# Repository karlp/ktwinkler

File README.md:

# kTwinkler

Replacement controller board for some "common" battery powered led fairy lights...

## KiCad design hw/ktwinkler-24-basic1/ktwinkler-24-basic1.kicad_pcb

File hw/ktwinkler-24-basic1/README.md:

# twinkler 24V garden
24v "field" bus lying around the garden, for smallish wires and enough power.
5V "led" bus light for the light strings I know I have
3.3v for an esp32
2x antiparallel led channels. (maybe a third if I can juggle the pins)
ufl antenna mount by default, but onboard PIFA as well.
designed to fit into some cheapish aliexpress waterproof junction boxes

# Bugs
This version won't boot with only the USB supply, it sags too much on startup.
This is because I didn't put enough decoupling on the esp32-c3.  Adding 10uF at
pin2 and 10uF at pin 31 fixed it, and is more inline with the hardware design guidelines
I believe earlier hardware had been sharing input caps with other portions of the boards,
so it wasn't noticed.

# Enhancements for a future version
* Remember rememeber, always add a nice place for a ground clip.
* you put a 3A supply down, it might have been nice to provide an output for that supply, instead
  of just burying it and only using it to power the drivers.

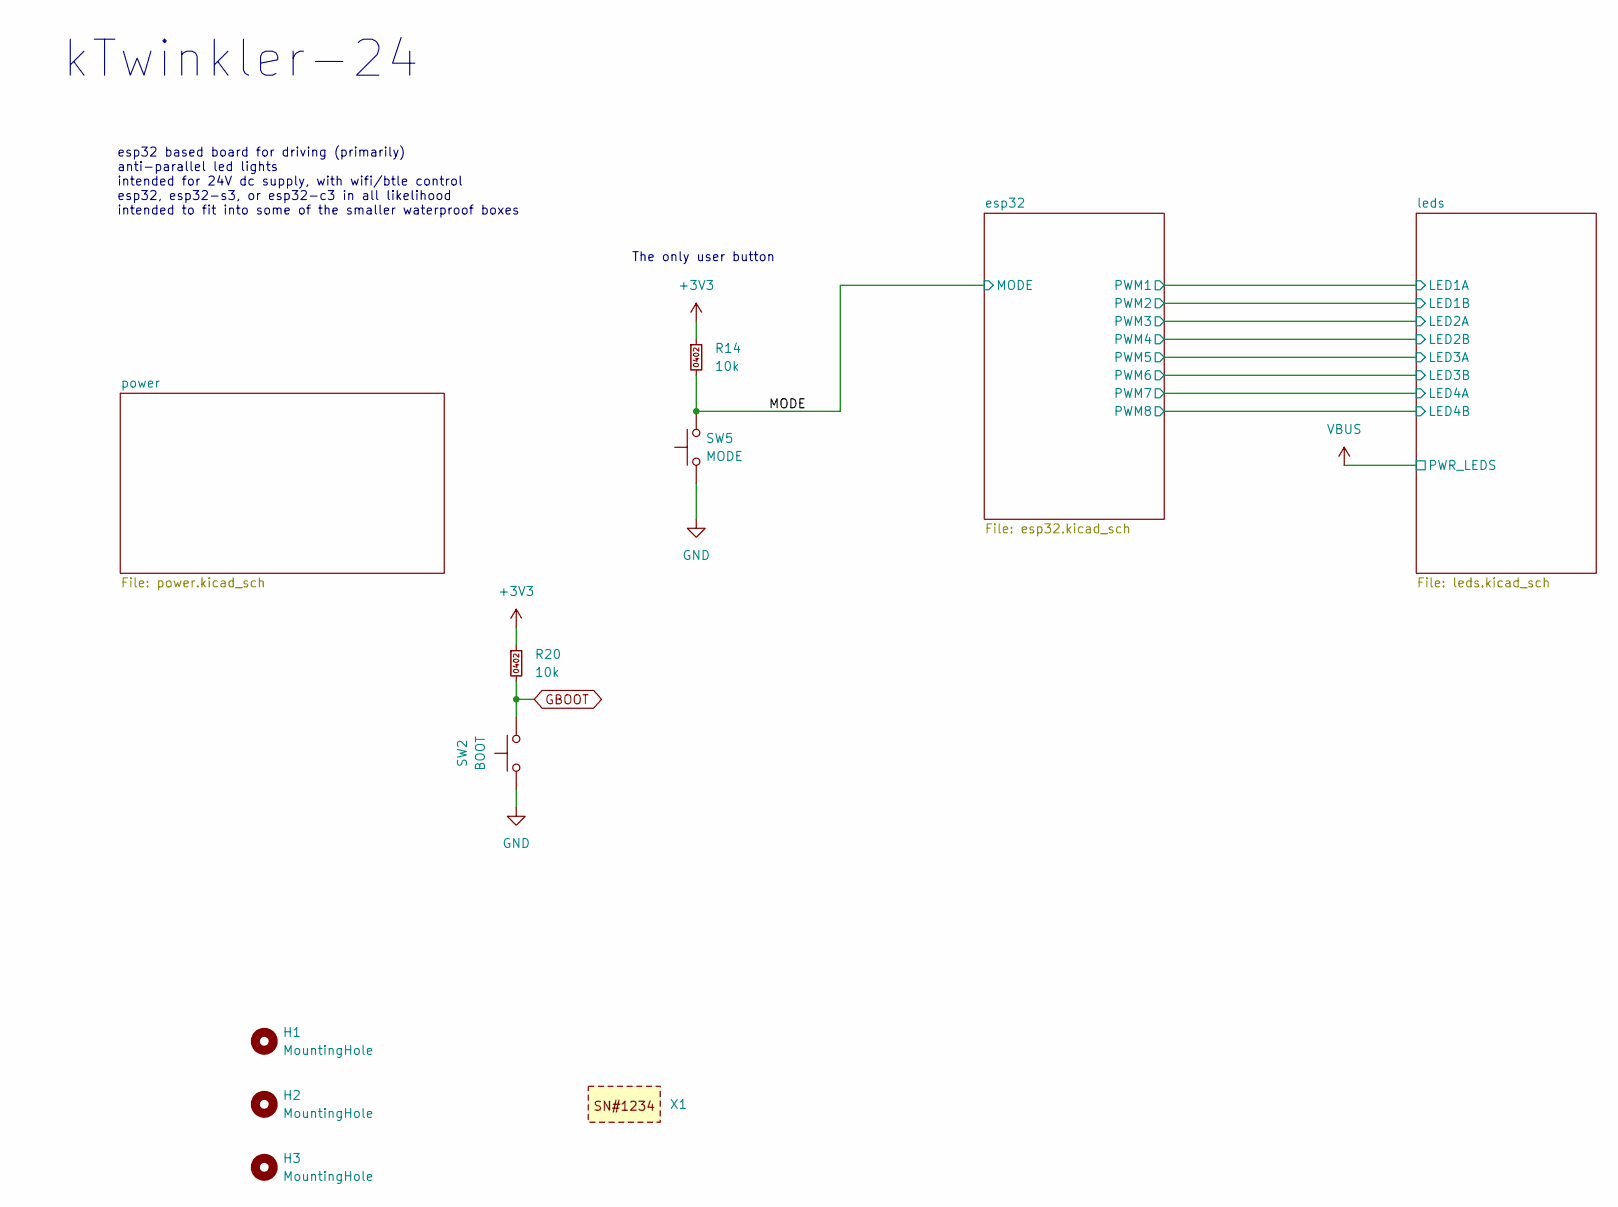
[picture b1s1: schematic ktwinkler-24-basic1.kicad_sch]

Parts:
H1, H2, H3: MountingHole; MountingHole_3.2mm_M3
R14, R20: 10k; R_0402_1005Metric; MPN 0402WGF1002TCE; LCSC Part # C25744
SW2: BOOT; SW_SPST_TL3342; MPN TS-1187A-B-A-B; jlcbasic basic
SW5: MODE; SW_SPST_TL3342; MPN TS-1187A-B-A-B; jlcbasic basic
X1: JLC_2D_BARCODE_8x8mm

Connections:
+3V3: R14.1, R20.1; also elsewhere on the board
/MODE: R14.2, SW5.2; also elsewhere on the board
GBOOT: R20.2, SW2.2; also elsewhere on the board
GND: SW2.1, SW5.1; also elsewhere on the board

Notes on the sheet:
esp32 based board for driving (primarily) anti-parallel led lights intended for 24V dc supply, with wifi/btle control esp32, esp32-s3, or esp32-c3 in all likelihood intended to fit into some of the smaller waterproof boxes
kTwinkler-24
The only user button

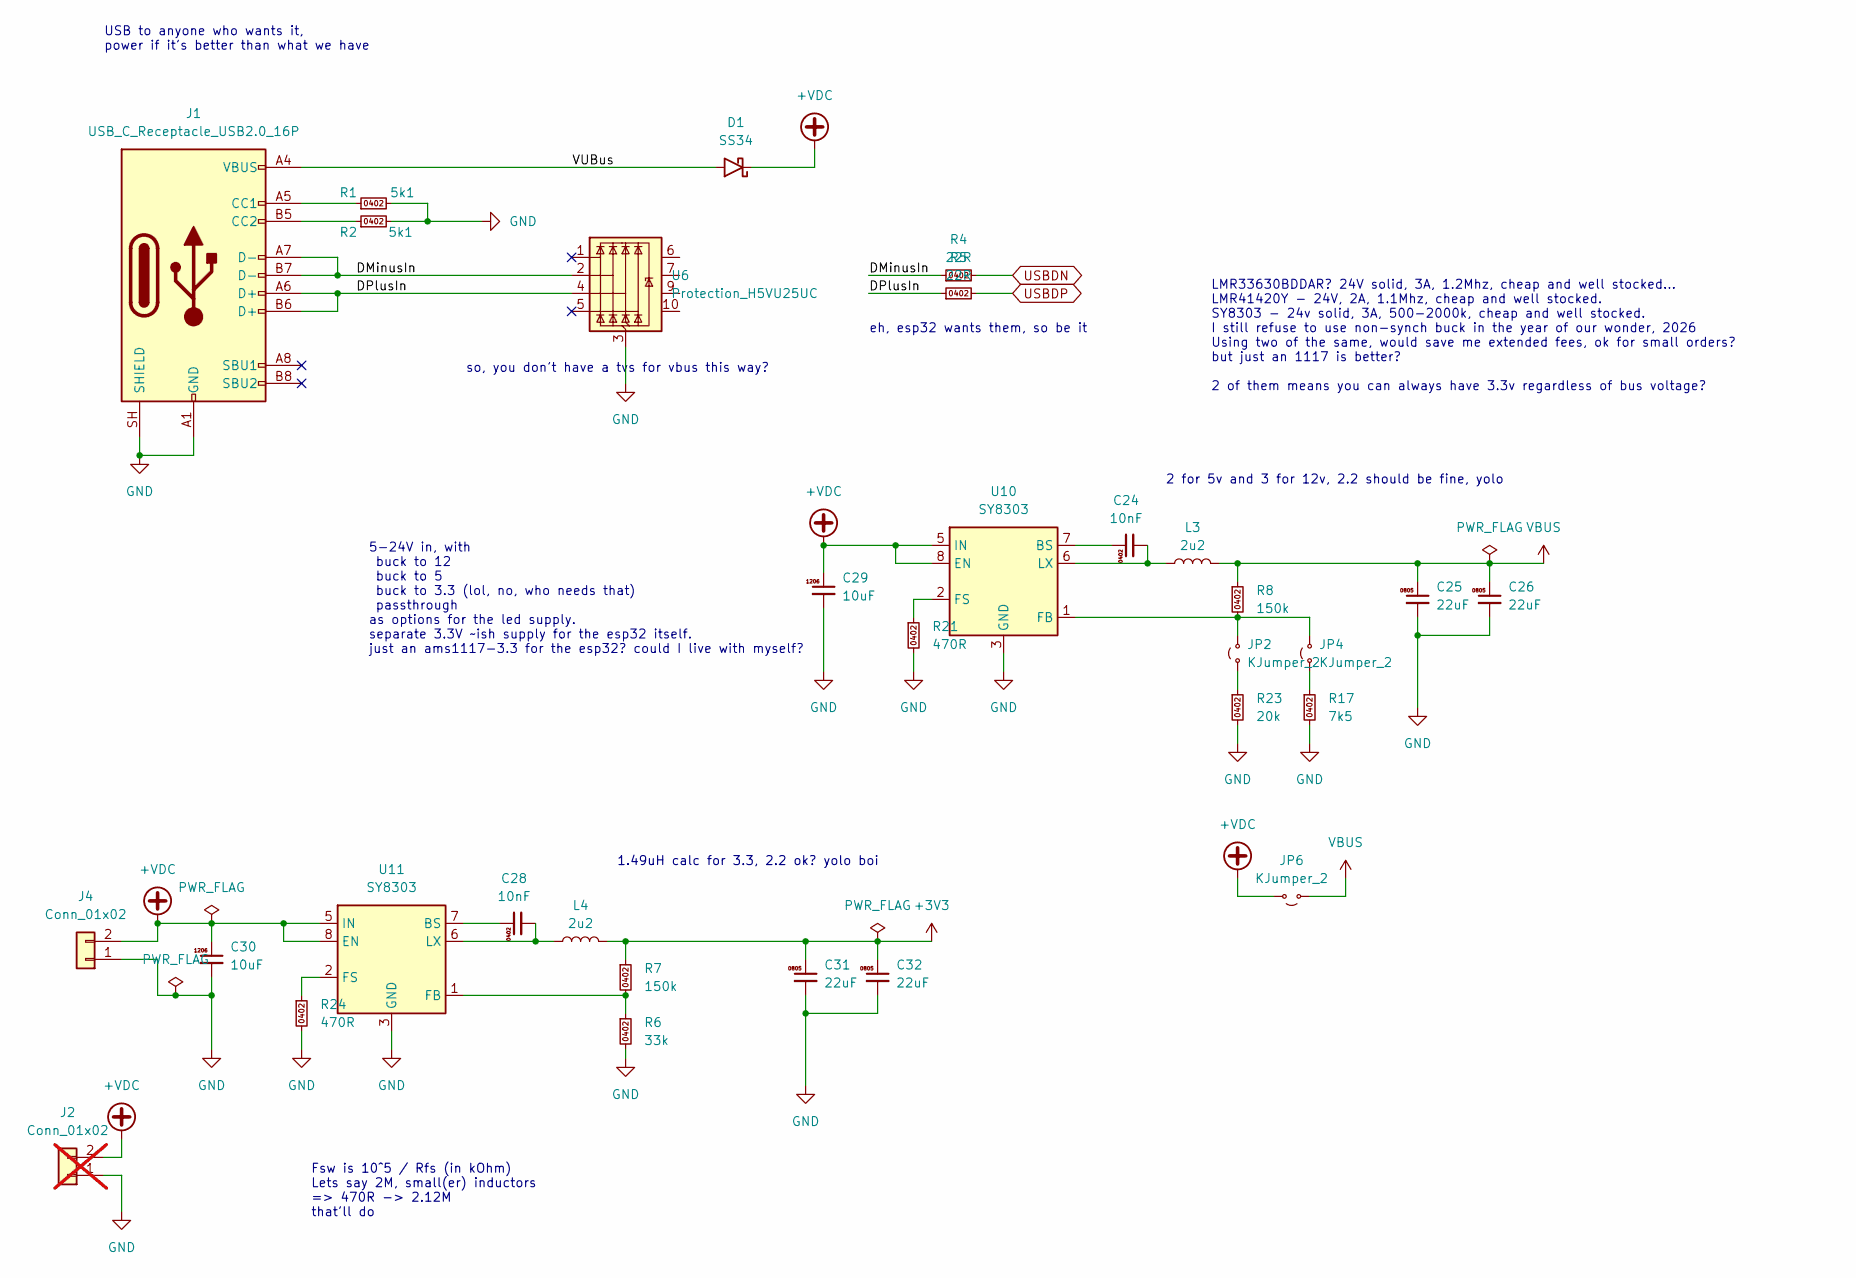
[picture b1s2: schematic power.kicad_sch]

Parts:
C24, C28: 10nF; C_0402_1005Metric; MPN CL05B103KB5NNNC; LCSC Part # C15195
C25, C26, C31, C32: 22uF; C_0805_2012Metric; MPN CL21A226MAQNNNE; LCSC Part # C45783
C29, C30: 10uF; C_1206_3216Metric; MPN CL31A106KBHNNNE; LCSC Part # C13585
D1: SS34; D_SMA; MPN SS34; LCSC Part # C8678
J1: USB_C_Receptacle_USB2.0_16P; USB_C_Receptacle_GCT_USB4105-xx-A_16P_TopMnt_Horizontal; MPN GT-USB-7010ASV; LCSC Part # C2988369
J2: Conn_01x02; PinHeader_1x02_P2.54mm_Vertical; not fitted
J4: Conn_01x02; PhoenixContact_MCV_1,5_2-G-3.81_1x02_P3.81mm_Vertical; MPN WJ15EDGVC-3.81-02P-14-00A; LCSC Part # C8396
JP2, JP4, JP6: KJumper_2; PinHeader_1x02_P2.54mm_Vertical
L3, L4: 2u2; L_Changjiang_FNR4030S; MPN FNR4030S2R2MT; LCSC Part # C167869
R1, R2: 5k1; R_0402_1005Metric; MPN 0402WGF5101TCE; LCSC Part # C25905
R4, R5: 22R; R_0402_1005Metric; MPN 0402WGF220JTCE; LCSC Part # C25092
R6: 33k; R_0402_1005Metric; MPN 0402WGF3302TCE; LCSC Part # C25779
R7, R8: 150k; R_0402_1005Metric; MPN 0402WGF1503TCE; LCSC Part # C25755
R17: 7k5; R_0402_1005Metric; MPN 0402WGF7501TCE; LCSC Part # C25918
R21, R24: 470R; R_0402_1005Metric; MPN 0402WGF4700TCE; LCSC Part # C25117
R23: 20k; R_0402_1005Metric; MPN 0402WGF2002TCE; LCSC Part # C25765
U6: Protection_H5VU25UC; Diodes_UDFN-10_1x2.5mm_P0.5mm; MPN H5VU25UC; jlcbasic preferred
U10, U11: SY8303; TSOT-23-8; LCSC Part # C97054

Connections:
+3V3: C31.1, C32.1, L4.2, R7.1; also elsewhere on the board
+VDC: C29.1, C30.1, D1.1 (K), J2.2, J4.2, JP6.2 (B), U10.5 (IN), U10.8 (EN), U11.5 (IN), U11.8 (EN)
/power/DMinusIn: J1.A7 (D-), J1.B7 (D-), R4.1, U6.2 (I/O2)
/power/DPlusIn: J1.A6 (D+), J1.B6 (D+), R5.1, U6.4 (I/O3)
/power/VUBus: D1.2 (A), J1.A4 (VBUS), J1.A9 (VBUS), J1.B4 (VBUS), J1.B9 (VBUS)
GND: C25.2, C26.2, C29.2, C30.2, C31.2, C32.2, J1.A1 (GND), J1.A12 (GND), J1.B1 (GND), J1.B12 (GND), J1.SH (SHIELD), J2.1, J4.1, R1.2, R2.2, R6.2, R17.2, R21.2, R23.2, R24.2, U6.3 (GND), U6.8 (GND), U10.3 (GND), U10.4 (GND), U11.3 (GND), U11.4 (GND); also elsewhere on the board
unnamed: J1.A5 (CC1), R1.1
unnamed: J1.B5 (CC2), R2.1
unnamed: JP2.1 (A), R23.1
unnamed: JP2.2 (B), JP4.2 (B), R8.2, U10.1 (FB)
unnamed: JP4.1 (A), R17.1
unnamed: C24.1, U10.7 (BS)
unnamed: R21.1, U10.2 (FS)
unnamed: C24.2, L3.1, U10.6 (LX)
unnamed: C28.1, U11.7 (BS)
unnamed: R6.1, R7.2, U11.1 (FB)
unnamed: R24.1, U11.2 (FS)
unnamed: C28.2, L4.1, U11.6 (LX)
USBDN: R4.2; also elsewhere on the board
USBDP: R5.2; also elsewhere on the board
VBUS: C25.1, C26.1, JP6.1 (A), L3.2, R8.1; also elsewhere on the board

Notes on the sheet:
LMR33630BDDAR? 24V solid, 3A, 1.2Mhz, cheap and well stocked... LMR41420Y - 24V, 2A, 1.1Mhz, cheap and well stocked. SY8303 - 24v solid, 3A, 500-2000k, cheap and well stocked. I still refuse to use non-synch buck in the year of our wonder, 2026 Using two of the same, would save me extended fees, ok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
5-24V in, with buck to 12 buck to 5 buck to 3.3 (lol, no, who needs that) passthrough as options for the led supply. separate 3.3V ~ish supply for the esp32 itself. just an ams1117-3.3 for the esp32? could I live with myself?
USB to anyone who wants it, power if it's better than what we have
so, you don't have a tvs for vbus this way?
1.49uH calc for 3.3, 2.2 ok? yolo boi
Fsw is 10^5 / Rfs (in kOhm) Lets say 2M, small(er) inductors => 470R -> 2.12M that'll do
eh, esp32 wants them, so be it
2 for 5v and 3 for 12v, 2.2 should be fine, yolo

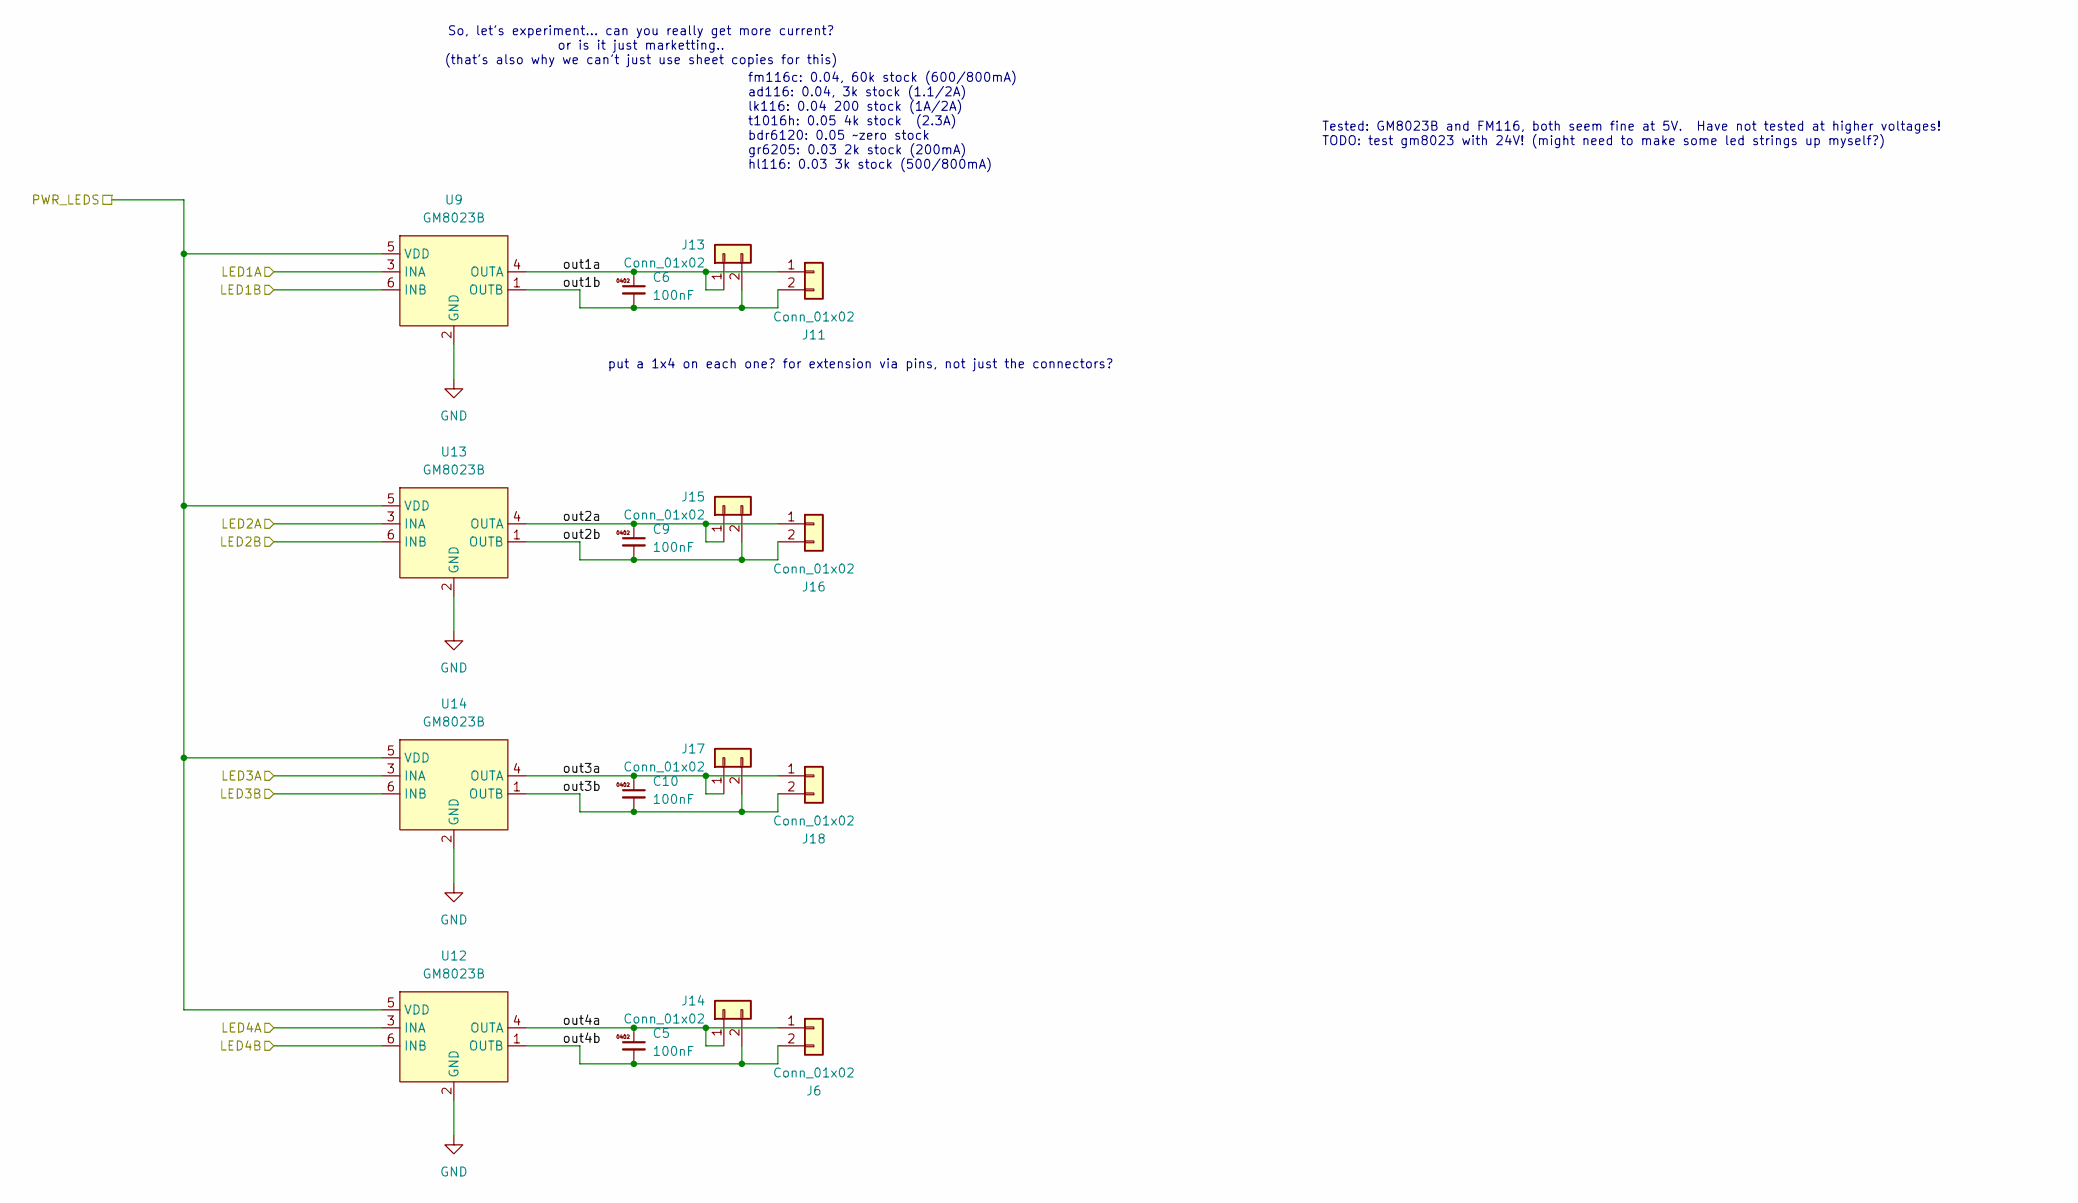
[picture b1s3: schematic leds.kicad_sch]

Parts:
C5, C6, C9, C10: 100nF; C_0402_1005Metric; MPN CL05B104KO5NNNC; LCSC Part # C1525
J6, J11, J16, J18: Conn_01x02; PhoenixContact_MCV_1,5_2-G-3.81_1x02_P3.81mm_Vertical; MPN WJ15EDGVC-3.81-02P-14-00A; LCSC Part # C8396
J13, J14, J15, J17: Conn_01x02; TestPoint_2Pads_Pitch2.54mm_Drill0.8mm
U9, U12, U13, U14: GM8023B; SOT-23-6; MPN GM8023B; LCSC Part # C269871

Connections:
/esp32/PWM1: U9.3 (INA); also elsewhere on the board
/esp32/PWM2: U9.6 (INB); also elsewhere on the board
/esp32/PWM3: U13.3 (INA); also elsewhere on the board
/esp32/PWM4: U13.6 (INB); also elsewhere on the board
/esp32/PWM5: U14.3 (INA); also elsewhere on the board
/esp32/PWM6: U14.6 (INB); also elsewhere on the board
/esp32/PWM7: U12.3 (INA); also elsewhere on the board
/esp32/PWM8: U12.6 (INB); also elsewhere on the board
/leds/out1a: C6.1, J11.1, J13.1, U9.4 (OUTA)
/leds/out1b: C6.2, J11.2, J13.2, U9.1 (OUTB)
/leds/out2a: C9.1, J15.1, J16.1, U13.4 (OUTA)
/leds/out2b: C9.2, J15.2, J16.2, U13.1 (OUTB)
/leds/out3a: C10.1, J17.1, J18.1, U14.4 (OUTA)
/leds/out3b: C10.2, J17.2, J18.2, U14.1 (OUTB)
/leds/out4a: C5.1, J6.1, J14.1, U12.4 (OUTA)
/leds/out4b: C5.2, J6.2, J14.2, U12.1 (OUTB)
GND: U9.2 (GND), U12.2 (GND), U13.2 (GND), U14.2 (GND); also elsewhere on the board
VBUS: U9.5 (VDD), U12.5 (VDD), U13.5 (VDD), U14.5 (VDD); also elsewhere on the board

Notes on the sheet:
So, let's experiment... can you really get more current? or is it just marketting.. (that's also why we can't just use sheet copies for this)
put a 1x4 on each one? for extension via pins, not just the connectors?
fm116c: 0.04, 60k stock (600/800mA) ad116: 0.04, 3k stock (1.1/2A) lk116: 0.04 200 stock (1A/2A) t1016h: 0.05 4k stock (2.3A) bdr6120: 0.05 ~zero stock gr6205: 0.03 2k stock (200mA) hl116: 0.03 3k stock (500/800mA)
Tested: GM8023B and FM116, both seem fine at 5V. Have not tested at higher voltages! TODO: test gm8023 with 24V! (might need to make some led strings up myself?)

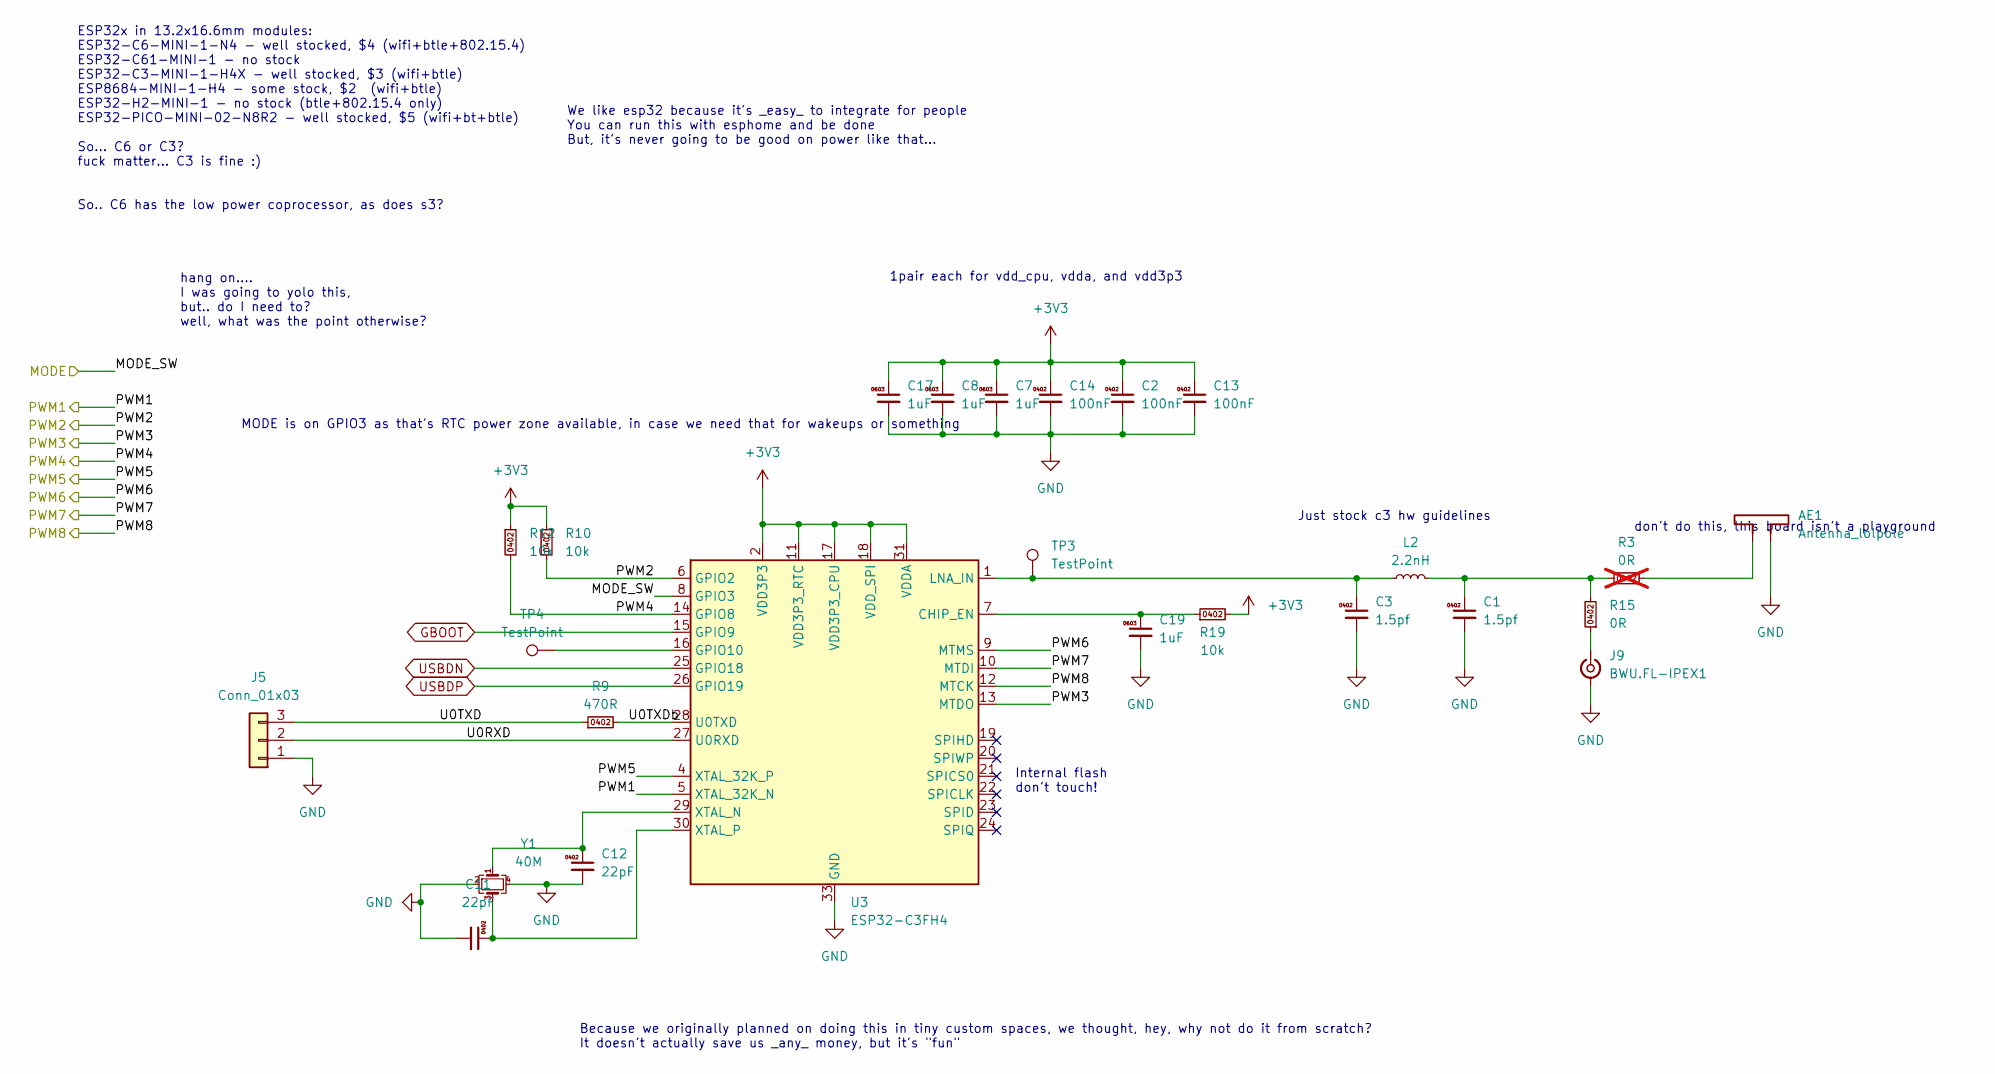
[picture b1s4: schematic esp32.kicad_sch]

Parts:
AE1: Antenna_lolpole; Texas_SWRA117D_2.4GHz_Left
C1, C3: 1.5pf; C_0402_1005Metric; MPN 0402CG1R5C500NT; LCSC Part # C1552
C2, C13, C14: 100nF; C_0402_1005Metric; MPN CL05B104KO5NNNC; LCSC Part # C1525
C7, C8, C17, C19: 1uF; C_0603_1608Metric; MPN CL10A105KB8NNNC; LCSC Part # C15849
C11, C12: 22pF; C_0402_1005Metric; MPN 0402CG220J500NT; LCSC Part # C1555
J5: Conn_01x03; PinHeader_1x03_P2.54mm_Vertical
J9: BWU.FL-IPEX1; U.FL_Hirose_U.FL-R-SMT-1_Vertical; MPN BWU.FL-IPEX1; LCSC Part # C5137195
L2: 2.2nH; L_0402_1005Metric; MPN LQG15HS2N2S02D; LCSC Part # C86061
R3: 0R; R_0402_1005Metric; MPN 0402WGF0000TCE; LCSC Part # C17168; not fitted
R9: 470R; R_0402_1005Metric; MPN 0402WGF4700TCE; LCSC Part # C25117
R10, R12, R19: 10k; R_0402_1005Metric; MPN 0402WGF1002TCE; LCSC Part # C25744
R15: 0R; R_0402_1005Metric; MPN 0402WGF0000TCE; LCSC Part # C17168
TP3, TP4: TestPoint; TestPoint_Pad_D1.0mm
U3: ESP32-C3FH4; QFN-32-1EP_5x5mm_P0.5mm_EP3.7x3.7mm; MPN ESP32-C3FH4; LCSC Part # C2858491
Y1: 40M; Crystal_SMD_2016-4Pin_2.0x1.6mm; MPN TAXM40M4ZHBCDT2T; LCSC Part # C424432

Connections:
+3V3: C2.1, C7.1, C8.1, C13.1, C14.1, C17.1, R10.1, R12.1, R19.2, U3.2 (VDD3P3), U3.3 (VDD3P3), U3.11 (VDD3P3_RTC), U3.17 (VDD3P3_CPU), U3.18 (VDD_SPI), U3.31 (VDDA), U3.32 (VDDA); also elsewhere on the board
/MODE: U3.8 (GPIO3); also elsewhere on the board
/esp32/PWM1: U3.5 (XTAL_32K_N); also elsewhere on the board
/esp32/PWM2: R10.2, U3.6 (GPIO2); also elsewhere on the board
/esp32/PWM3: U3.13 (MTDO); also elsewhere on the board
/esp32/PWM4: R12.2, U3.14 (GPIO8); also elsewhere on the board
/esp32/PWM5: U3.4 (XTAL_32K_P); also elsewhere on the board
/esp32/PWM6: U3.9 (MTMS); also elsewhere on the board
/esp32/PWM7: U3.10 (MTDI); also elsewhere on the board
/esp32/PWM8: U3.12 (MTCK); also elsewhere on the board
/esp32/U0RXD: J5.2, U3.27 (U0RXD)
/esp32/U0TXD: J5.3, R9.1
/esp32/U0TXDb: R9.2, U3.28 (U0TXD)
GBOOT: U3.15 (GPIO9); also elsewhere on the board
GND: AE1.2, C1.2, C2.2, C3.2, C7.2, C8.2, C11.2, C12.2, C13.2, C14.2, C17.2, C19.2, J5.1, J9.2 (Ext), U3.33 (GND), Y1.2, Y1.4; also elsewhere on the board
unnamed: AE1.1, R3.2
unnamed: C1.1, L2.2, R3.1, R15.2
unnamed: J9.1 (In), R15.1
unnamed: C19.1, R19.1, U3.7 (CHIP_EN)
unnamed: TP4.1 (1_1), U3.16 (GPIO10)
unnamed: C3.1, L2.1, TP3.1 (1_1), U3.1 (LNA_IN)
unnamed: C12.1, U3.29 (XTAL_N), Y1.1
unnamed: C11.1, U3.30 (XTAL_P), Y1.3
USBDN: U3.25 (GPIO18); also elsewhere on the board
USBDP: U3.26 (GPIO19); also elsewhere on the board

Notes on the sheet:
don't do this, this board isn't a playground
Internal flash don't touch!
hang on.... I was going to yolo this, but.. do I need to? well, what was the point otherwise?
MODE is on GPIO3 as that's RTC power zone available, in case we need that for wakeups or something
ESP32x in 13.2x16.6mm modules: ESP32-C6-MINI-1-N4 - well stocked, $4 (wifi+btle+802.15.4) ESP32-C61-MINI-1 - no stock ESP32-C3-MINI-1-H4X - well stocked, $3 (wifi+btle) ESP8684-MINI-1-H4 - some stock, $2 (wifi+btle) ESP32-H2-MINI-1 - no stock (btle+802.15.4 only) ESP32-PICO-MINI-02-N8R2 - well stoc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
Because we originally planned on doing this in tiny custom spaces, we thought, hey, why not do it from scratch? It doesn't actually save us _any_ money, but it's "fun"
We like esp32 because it's _easy_ to integrate for people You can run this with esphome and be done But, it's never going to be good on power like that...
1pair each for vdd_cpu, vdda, and vdd3p3
Just stock c3 hw guidelines

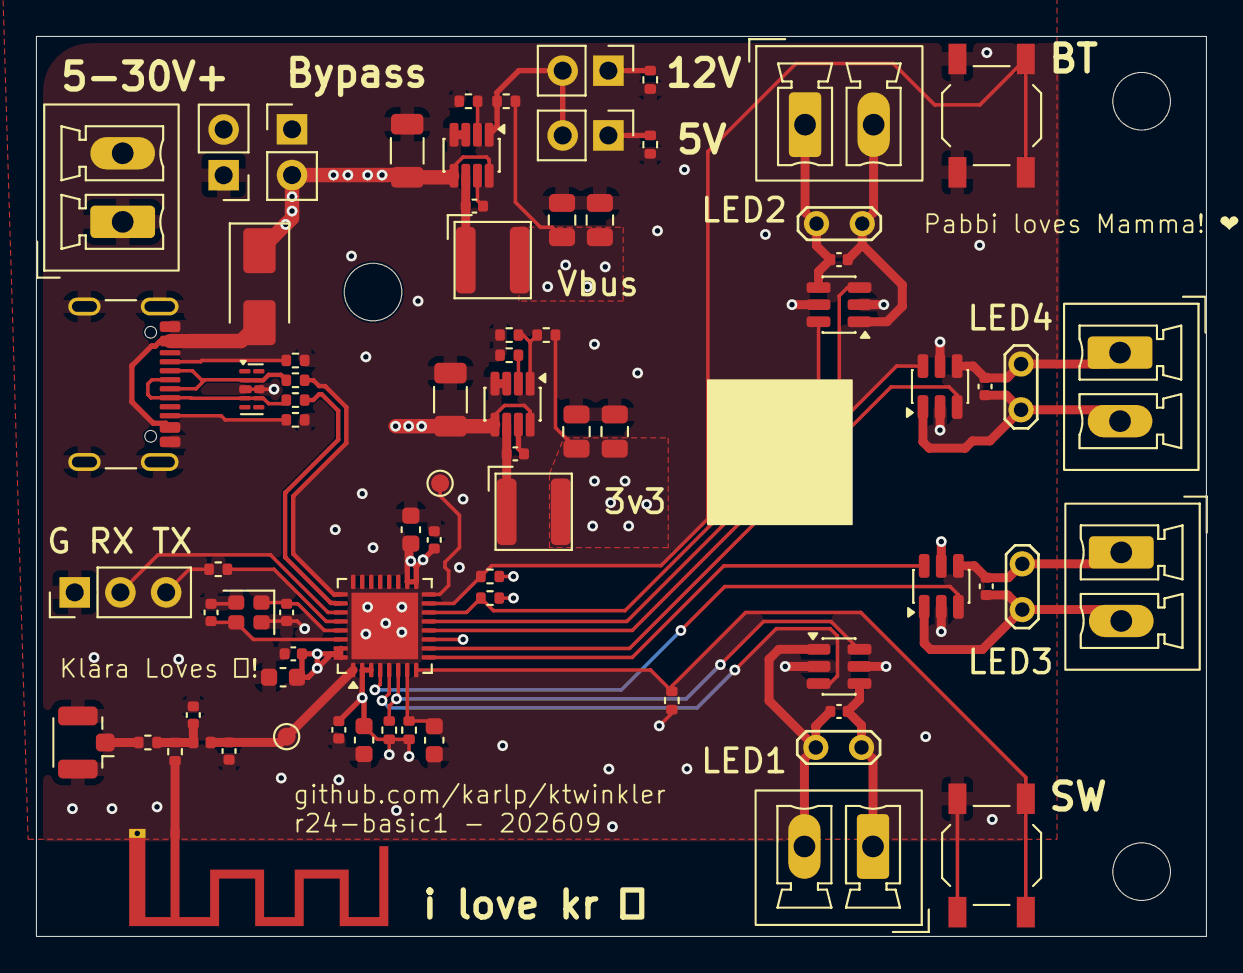
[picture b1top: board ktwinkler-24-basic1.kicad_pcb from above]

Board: 4 copper layers, 65.0 x 50.0 mm, 80 parts (0 on the bottom side), 50 nets.

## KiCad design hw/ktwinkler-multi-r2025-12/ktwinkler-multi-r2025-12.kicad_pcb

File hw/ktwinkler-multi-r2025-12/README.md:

# twinkler multi
Instead of trying to make the tiniest little thing stuffed into a battery case, when we already know that they have buttons on different sides and locations, so it would never be one size fits all anyway, let's make something a bit different.

Just make it as a controller board, with a couple of channels, so you can just plug in some strings chopped off cheap kits.  Also. let's play with two cpus, and some different motor controllers to see what's "best"

Try allll the things!

# To try
* different cheap motor chips
* smt screw mount shits.
* battery ... wots?

# Errors/lessons from first production run
lol, the H5VU25UC uni tvs I chose, I totally misread the internal schematic, and connected it with 3/8 being vcc/gnd, ala bidir.  Soooo, that has a nice built in short :)  Easy fix, remove the tvs on these boards, but need to fix the part in my lib!

lol2, PWM3-8 on ESP32 are totally unusable, connected to internal spi.  I could have sworn I'd checked that? not many actually free IOs
on C3 :(  Need to cut all traces, then it can be flashed and runs ok, with the limited set remaining.  Should have used the jtag pins, and the strapping pins instead :(

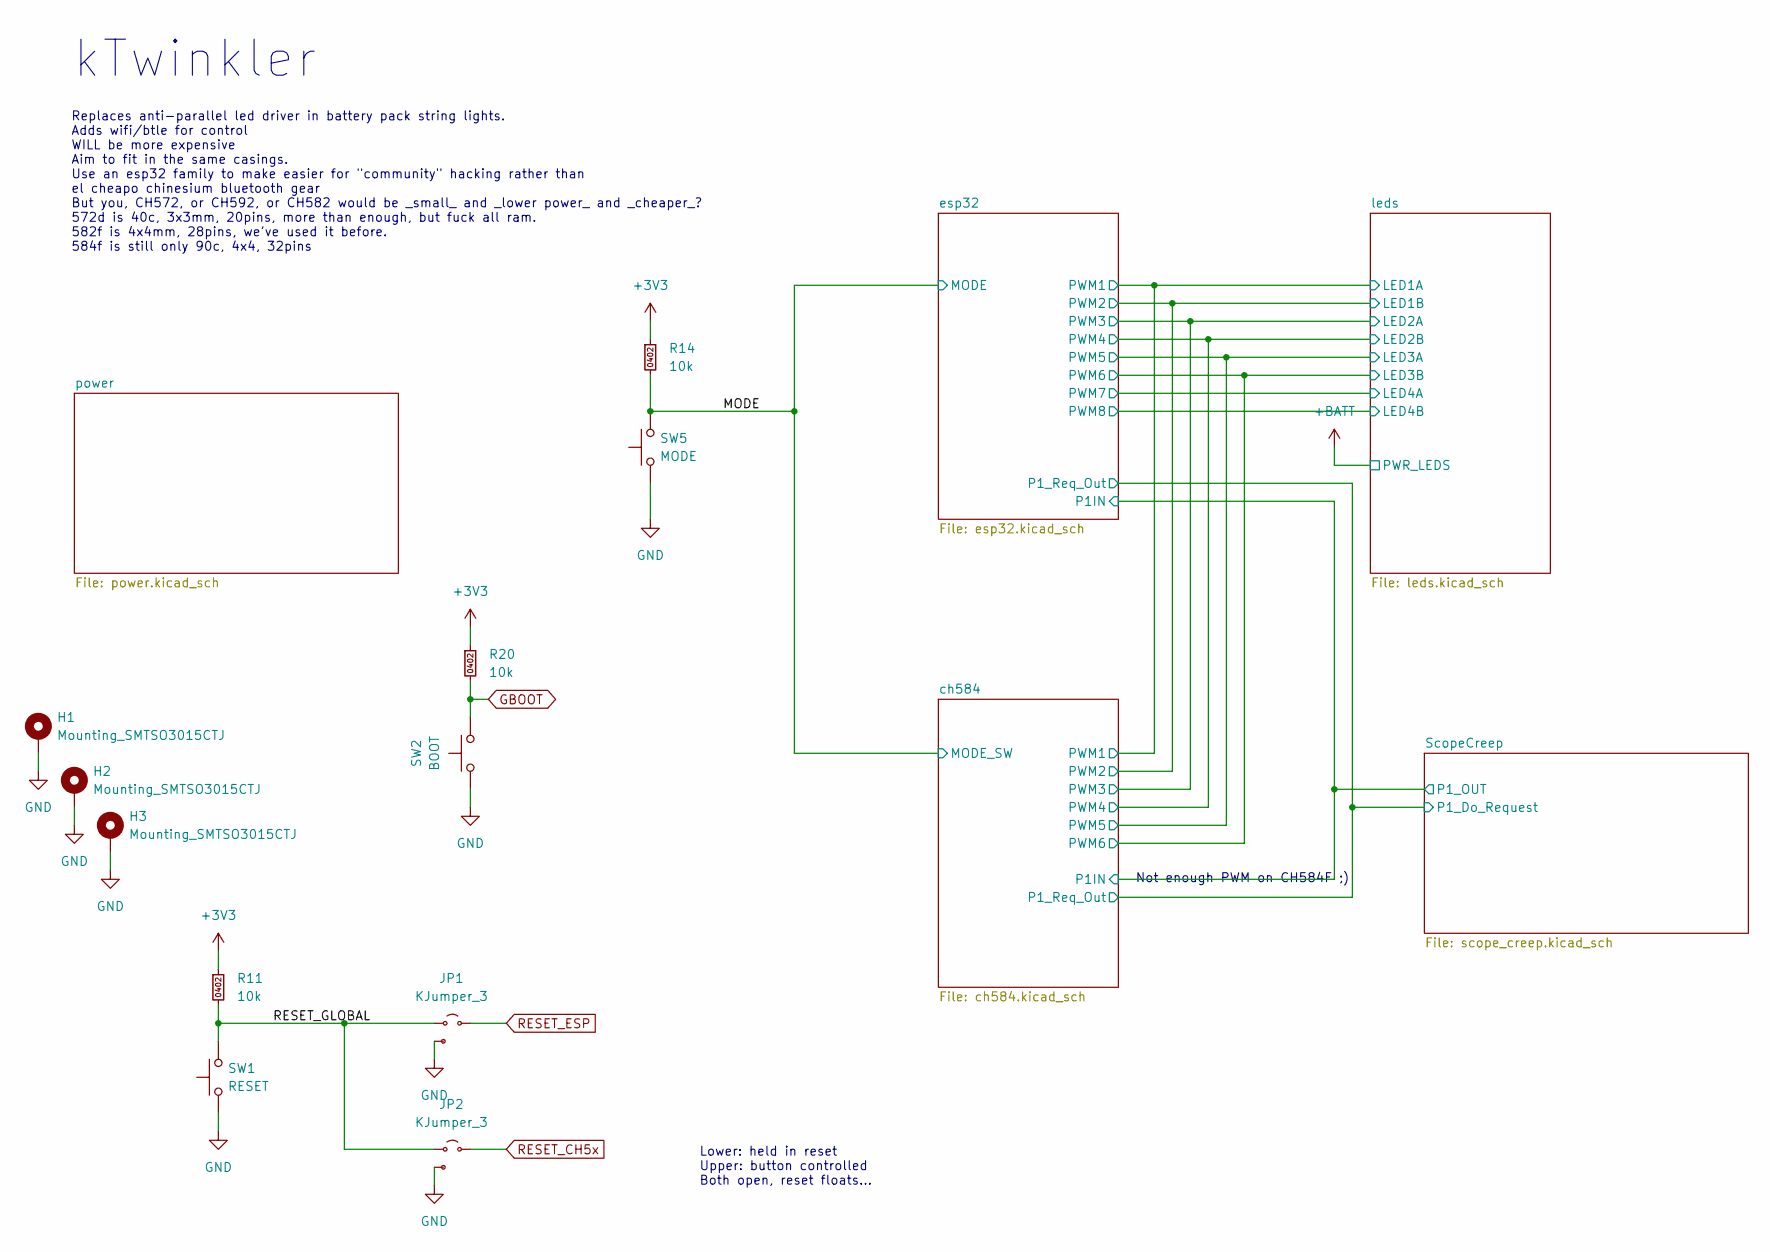
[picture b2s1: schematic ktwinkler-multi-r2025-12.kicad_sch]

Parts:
H1, H2, H3: Mounting_SMTSO3015CTJ; Mounting_SMTSO_M3_ALT2; MPN SMTSO3015CTJ; jlcbasic 0
JP1, JP2: KJumper_3; PinHeader_1x03_P2.54mm_Vertical
R11, R14, R20: 10k; R_0402_1005Metric; MPN 0402WGF1002TCE; LCSC Part # C25744
SW1: RESET; SW_SPST_TL3342; MPN TS-1187A-B-A-B; jlcbasic basic
SW2: BOOT; SW_SPST_TL3342; MPN TS-1187A-B-A-B; jlcbasic basic
SW5: MODE; SW_SPST_TL3342; MPN TS-1187A-B-A-B; jlcbasic basic

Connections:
+3V3: R11.1, R14.1, R20.1; also elsewhere on the board
/MODE: R14.2, SW5.2; also elsewhere on the board
/RESET_GLOBAL: JP1.1 (A), JP2.1 (A), R11.2, SW1.2
GBOOT: R20.2, SW2.2; also elsewhere on the board
GND: H1.1 (1_1), H2.1 (1_1), H3.1 (1_1), JP1.3 (B), JP2.3 (B), SW1.1, SW2.1, SW5.1; also elsewhere on the board
RESET_CH5x: JP2.2 (Comm); also elsewhere on the board
RESET_ESP: JP1.2 (Comm); also elsewhere on the board

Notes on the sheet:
Not enough PWM on CH584F ;)
Replaces anti-parallel led driver in battery pack string lights. Adds wifi/btle for control WILL be more expensive Aim to fit in the same casings. Use an esp32 family to make easier for "community" hacking rather than el cheapo chinesium bluetooth gear But you, CH572, or CH592, or CH582 would be _s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
Lower: held in reset Upper: button controlled Both open, reset floats...
kTwinkler

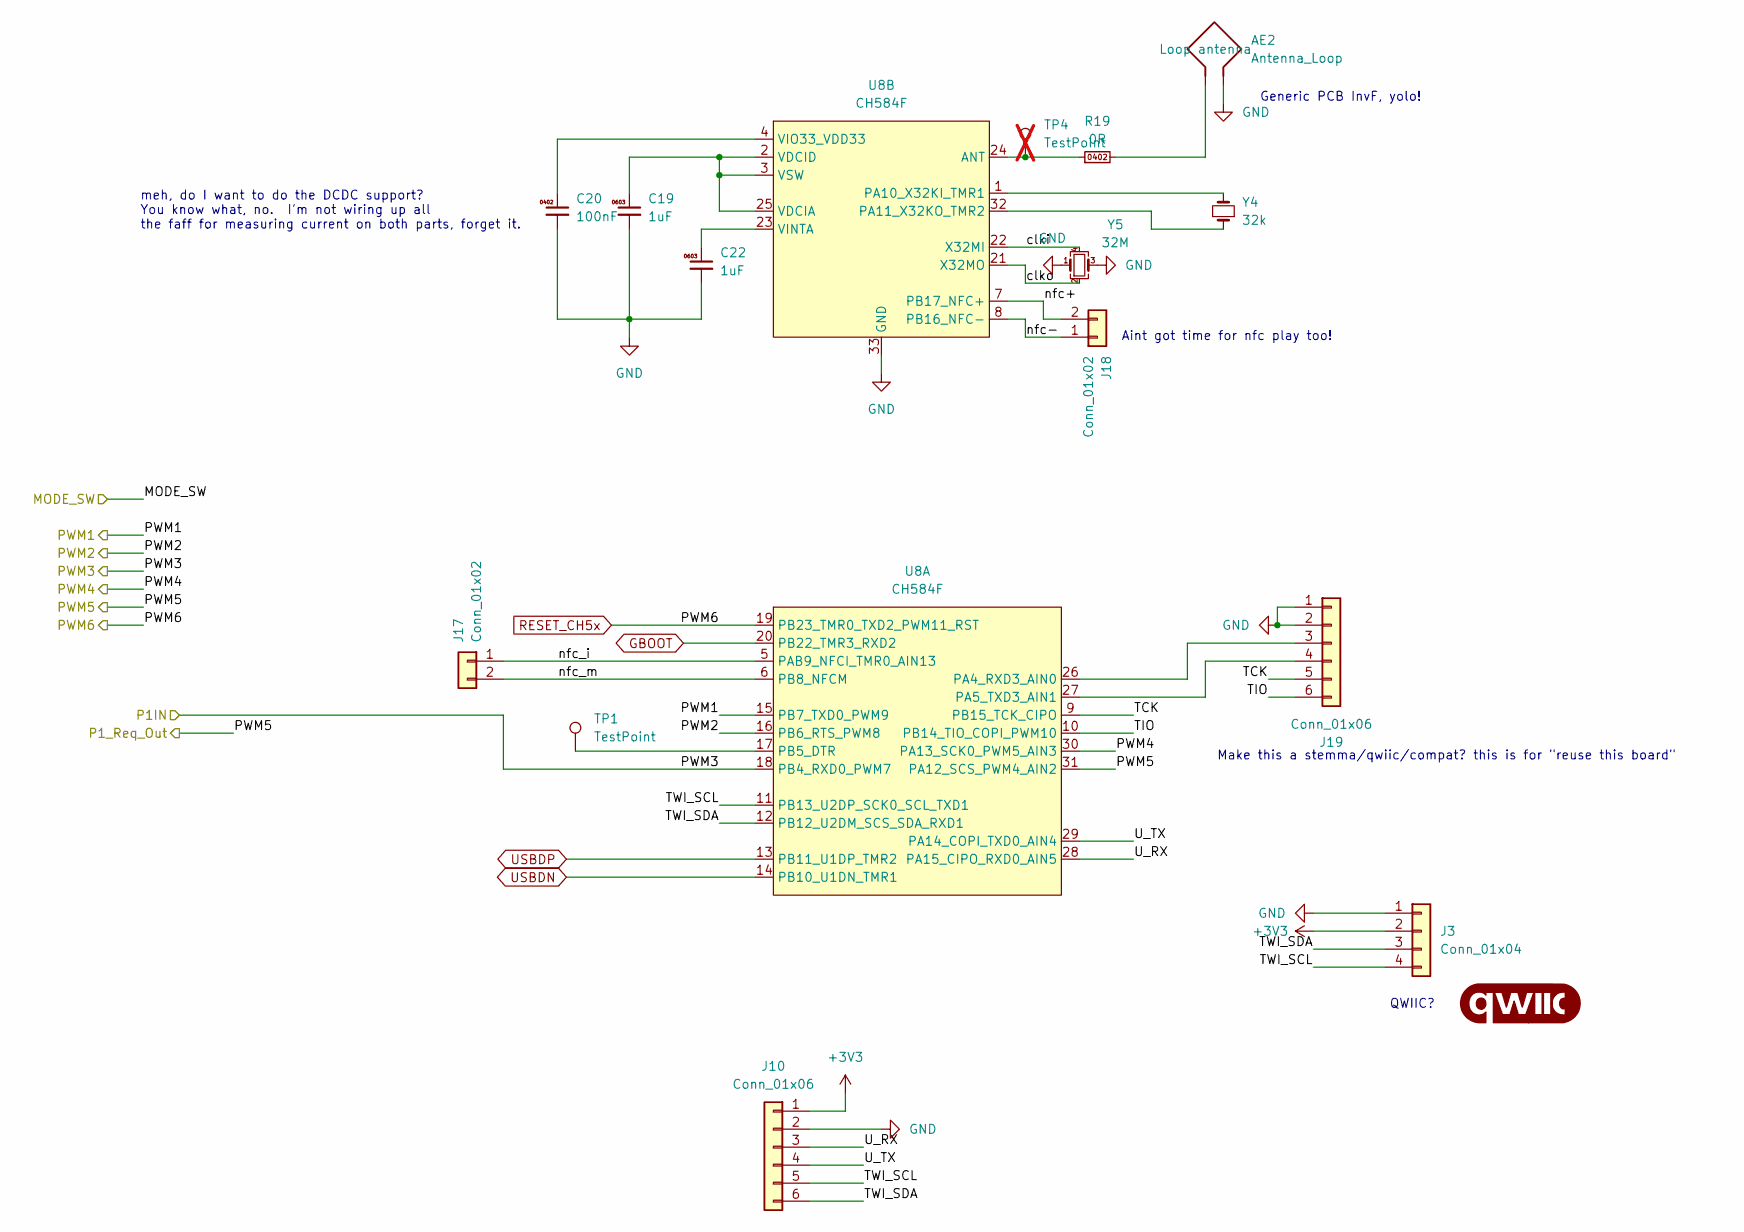
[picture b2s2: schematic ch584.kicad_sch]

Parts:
AE2: Antenna_Loop; ANT-F-1-2.4G-1.6MM-FR4-WCH-FLIP
C19, C22: 1uF; C_0603_1608Metric; MPN CL10A105KB8NNNC; LCSC Part # C15849
C20: 100nF; C_0402_1005Metric; MPN CL05B104KO5NNNC; LCSC Part # C1525
G1: qwiic_Logo; qwiic_4mm
J3: Conn_01x04; JST_SH_SM04B-SRSS-TB_1x04-1MP_P1.00mm_Horizontal; MPN 1.0-4PWB; LCSC Part # C2905006
J10, J19: Conn_01x06; PinHeader_1x06_P2.54mm_Vertical
J17, J18: Conn_01x02; TestPoint_2Pads_Pitch2.54mm_Drill0.8mm
R19: 0R; R_0402_1005Metric; MPN 0402WGF0000TCE; LCSC Part # C17168
TP1: TestPoint; TestPoint_THTPad_D1.0mm_Drill0.5mm
TP4: TestPoint; TestPoint_Pad_D1.0mm; not fitted
U8: CH584F; QFN-32-1EP_4x4mm_P0.4mm_EP2.65x2.65mm; MPN CH584F; LCSC Part # C42381468
Y4: 32k; Crystal_SMD_3215-2Pin_3.2x1.5mm; MPN Q13FC13500004; LCSC Part # C32346
Y5: 32M; Crystal_SMD_2016-4Pin_2.0x1.6mm; MPN XTM20032000DT00351005; LCSC Part # C37635332

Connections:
+3V3: J3.2, J10.1; also elsewhere on the board
/ch584/PWM1: U8.15 (PB7_TXD0_PWM9); also elsewhere on the board
/ch584/PWM2: U8.16 (PB6_RTS_PWM8); also elsewhere on the board
/ch584/PWM3: U8.18 (PB4_RXD0_PWM7); also elsewhere on the board
/ch584/PWM4: U8.30 (PA13_SCK0_PWM5_AIN3); also elsewhere on the board
/ch584/PWM5: U8.31 (PA12_SCS_PWM4_AIN2); also elsewhere on the board
/ch584/TCK: J19.5, U8.9 (PB15_TCK_CIPO)
/ch584/TIO: J19.6, U8.10 (PB14_TIO_COPI_PWM10)
/ch584/TWI_SCL: J3.4, J10.5, U8.11 (PB13_U2DP_SCK0_SCL_TXD1)
/ch584/TWI_SDA: J3.3, J10.6, U8.12 (PB12_U2DM_SCS_SDA_RXD1)
/ch584/U_RX: J10.3, U8.28 (PA15_CIPO_RXD0_AIN5)
/ch584/U_TX: J10.4, U8.29 (PA14_COPI_TXD0_AIN4)
/ch584/clki: U8.22 (X32MI), Y5.4
/ch584/clko: U8.21 (X32MO), Y5.2
/ch584/nfc+: J18.2, U8.7 (PB17_NFC+)
/ch584/nfc-: J18.1, U8.8 (PB16_NFC-)
/ch584/nfc_i: J17.1, U8.5 (PAB9_NFCI_TMR0_AIN13)
/ch584/nfc_m: J17.2, U8.6 (PB8_NFCM)
GBOOT: U8.20 (PB22_TMR3_RXD2); also elsewhere on the board
GND: AE2.2, C19.2, C20.2, C22.2, J3.1, J10.2, J19.1, J19.2, U8.33 (GND), Y5.1, Y5.3; also elsewhere on the board
unnamed: AE2.1, R19.2
unnamed: J19.3, U8.26 (PA4_RXD3_AIN0)
unnamed: J19.4, U8.27 (PA5_TXD3_AIN1)
unnamed: TP1.1 (1_1), U8.17 (PB5_DTR)
unnamed: R19.1, TP4.1 (1_1), U8.24 (ANT)
unnamed: U8.1 (PA10_X32KI_TMR1), Y4.2
unnamed: U8.32 (PA11_X32KO_TMR2), Y4.1
unnamed: C19.1, U8.2 (VDCID), U8.3 (VSW), U8.25 (VDCIA)
unnamed: C22.1, U8.23 (VINTA)
unnamed: C20.1, U8.4 (VIO33_VDD33)
RESET_CH5x: U8.19 (PB23_TMR0_TXD2_PWM11_RST); also elsewhere on the board
USBDN: U8.14 (PB10_U1DN_TMR1); also elsewhere on the board
USBDP: U8.13 (PB11_U1DP_TMR2); also elsewhere on the board

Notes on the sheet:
meh, do I want to do the DCDC support? You know what, no. I'm not wiring up all the faff for measuring current on both parts, forget it.
Generic PCB InvF, yolo!
QWIIC?
Aint got time for nfc play too!
Make this a stemma/qwiic/compat? this is for "reuse this board"
